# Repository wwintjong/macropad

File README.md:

# Macropad

My take on a macropad that I think will suit me. The layout is a 5x4 keys with hot-swappable switch and LED. Current iteration has no knobs or display implemented, but that is an idea for future versions. Next step is to design enclosure for the pad.

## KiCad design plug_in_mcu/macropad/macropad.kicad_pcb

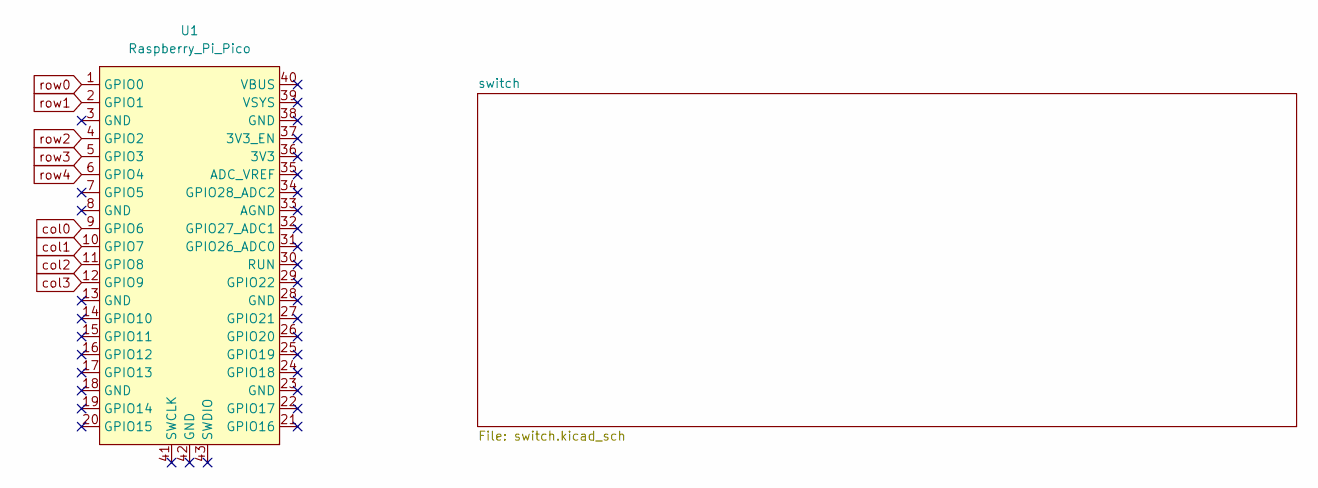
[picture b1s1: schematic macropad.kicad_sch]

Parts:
U1: Raspberry_Pi_Pico

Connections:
col0: U1.9 (GPIO6); also elsewhere on the board
col1: U1.10 (GPIO7); also elsewhere on the board
col2: U1.11 (GPIO8); also elsewhere on the board
col3: U1.12 (GPIO9); also elsewhere on the board
row0: U1.1 (GPIO0); also elsewhere on the board
row1: U1.2 (GPIO1); also elsewhere on the board
row2: U1.4 (GPIO2); also elsewhere on the board
row3: U1.5 (GPIO3); also elsewhere on the board
row4: U1.6 (GPIO4); also elsewhere on the board

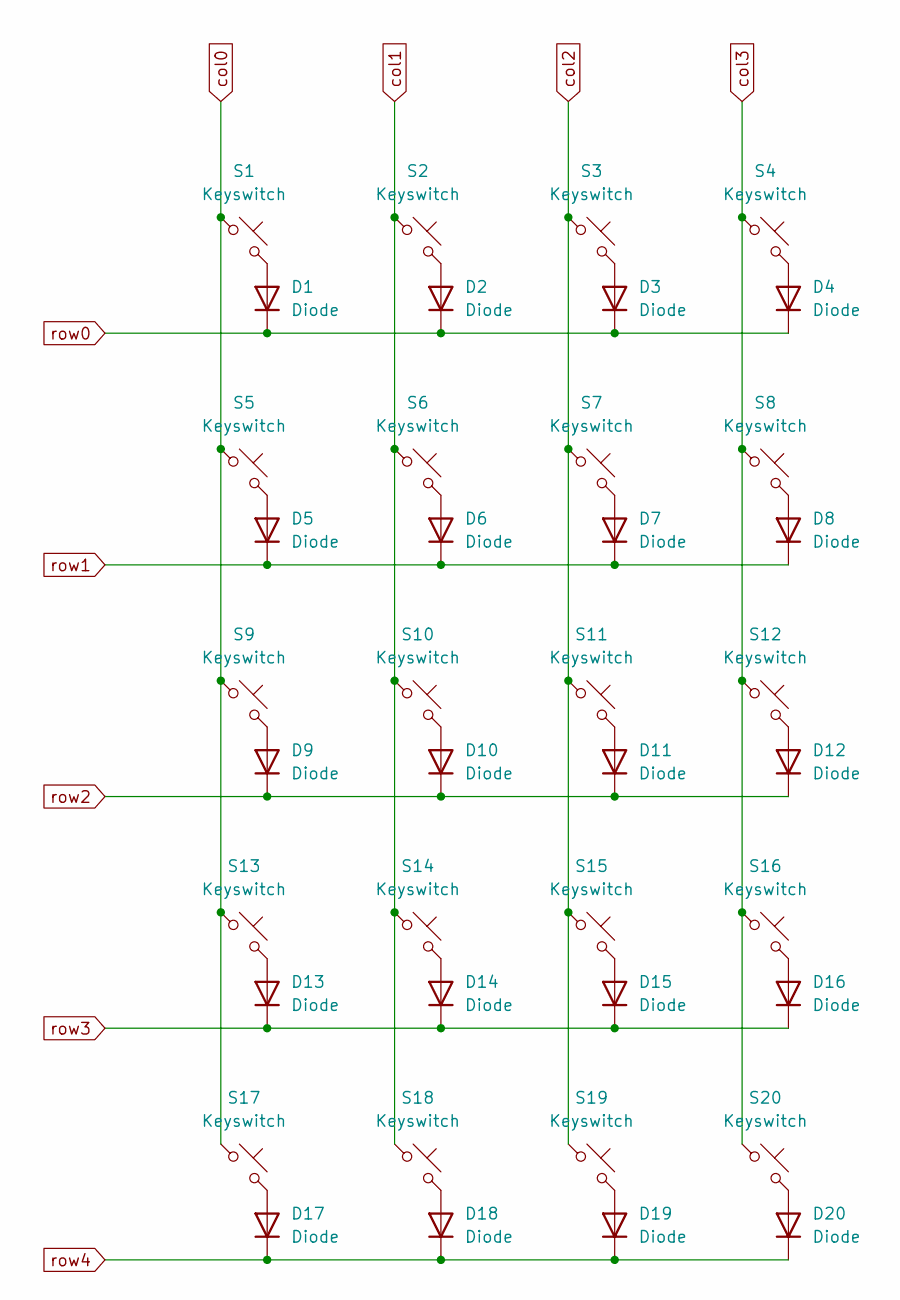
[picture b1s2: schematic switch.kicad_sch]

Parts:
D1, D2, D3, D4, D5, D6, D7, D8, D9, D10, D11, D12, D13, D14, D15, D16, D17, D18, D19, D20: Diode; D_SOD-123
S1, S2, S3, S4, S5, S6, S7, S8, S9, S10, S11, S12, S13, S14, S15, S16, S17, S18, S19, S20: Keyswitch; CherryMX_1.00u_KailhSocket

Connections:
unnamed: D1.2 (A), S1.2
unnamed: D2.2 (A), S2.2
unnamed: D3.2 (A), S3.2
unnamed: D4.2 (A), S4.2
unnamed: D5.2 (A), S5.2
unnamed: D6.2 (A), S6.2
unnamed: D7.2 (A), S7.2
unnamed: D8.2 (A), S8.2
unnamed: D9.2 (A), S9.2
unnamed: D10.2 (A), S10.2
unnamed: D11.2 (A), S11.2
unnamed: D12.2 (A), S12.2
unnamed: D13.2 (A), S13.2
unnamed: D14.2 (A), S14.2
unnamed: D15.2 (A), S15.2
unnamed: D16.2 (A), S16.2
unnamed: D17.2 (A), S17.2
unnamed: D18.2 (A), S18.2
unnamed: D19.2 (A), S19.2
unnamed: D20.2 (A), S20.2
col0: S1.1, S5.1, S9.1, S13.1, S17.1; also elsewhere on the board
col1: S2.1, S6.1, S10.1, S14.1, S18.1; also elsewhere on the board
col2: S3.1, S7.1, S11.1, S15.1, S19.1; also elsewhere on the board
col3: S4.1, S8.1, S12.1, S16.1, S20.1; also elsewhere on the board
row0: D1.1 (K), D2.1 (K), D3.1 (K), D4.1 (K); also elsewhere on the board
row1: D5.1 (K), D6.1 (K), D7.1 (K), D8.1 (K); also elsewhere on the board
row2: D9.1 (K), D10.1 (K), D11.1 (K), D12.1 (K); also elsewhere on the board
row3: D13.1 (K), D14.1 (K), D15.1 (K), D16.1 (K); also elsewhere on the board
row4: D17.1 (K), D18.1 (K), D19.1 (K), D20.1 (K); also elsewhere on the board

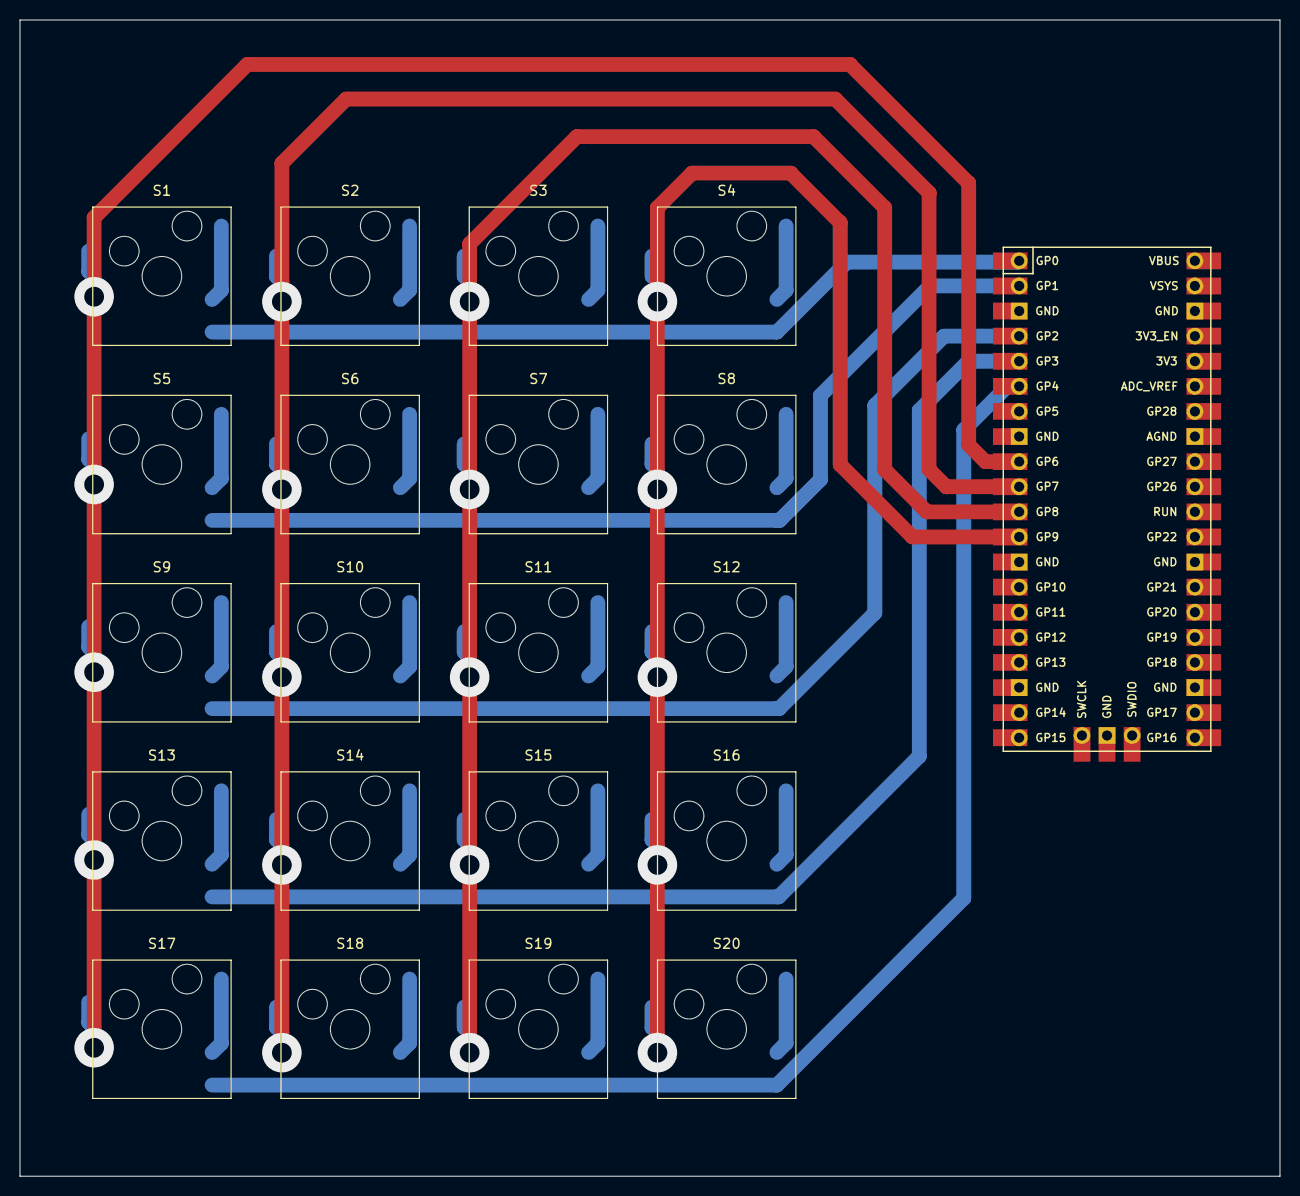
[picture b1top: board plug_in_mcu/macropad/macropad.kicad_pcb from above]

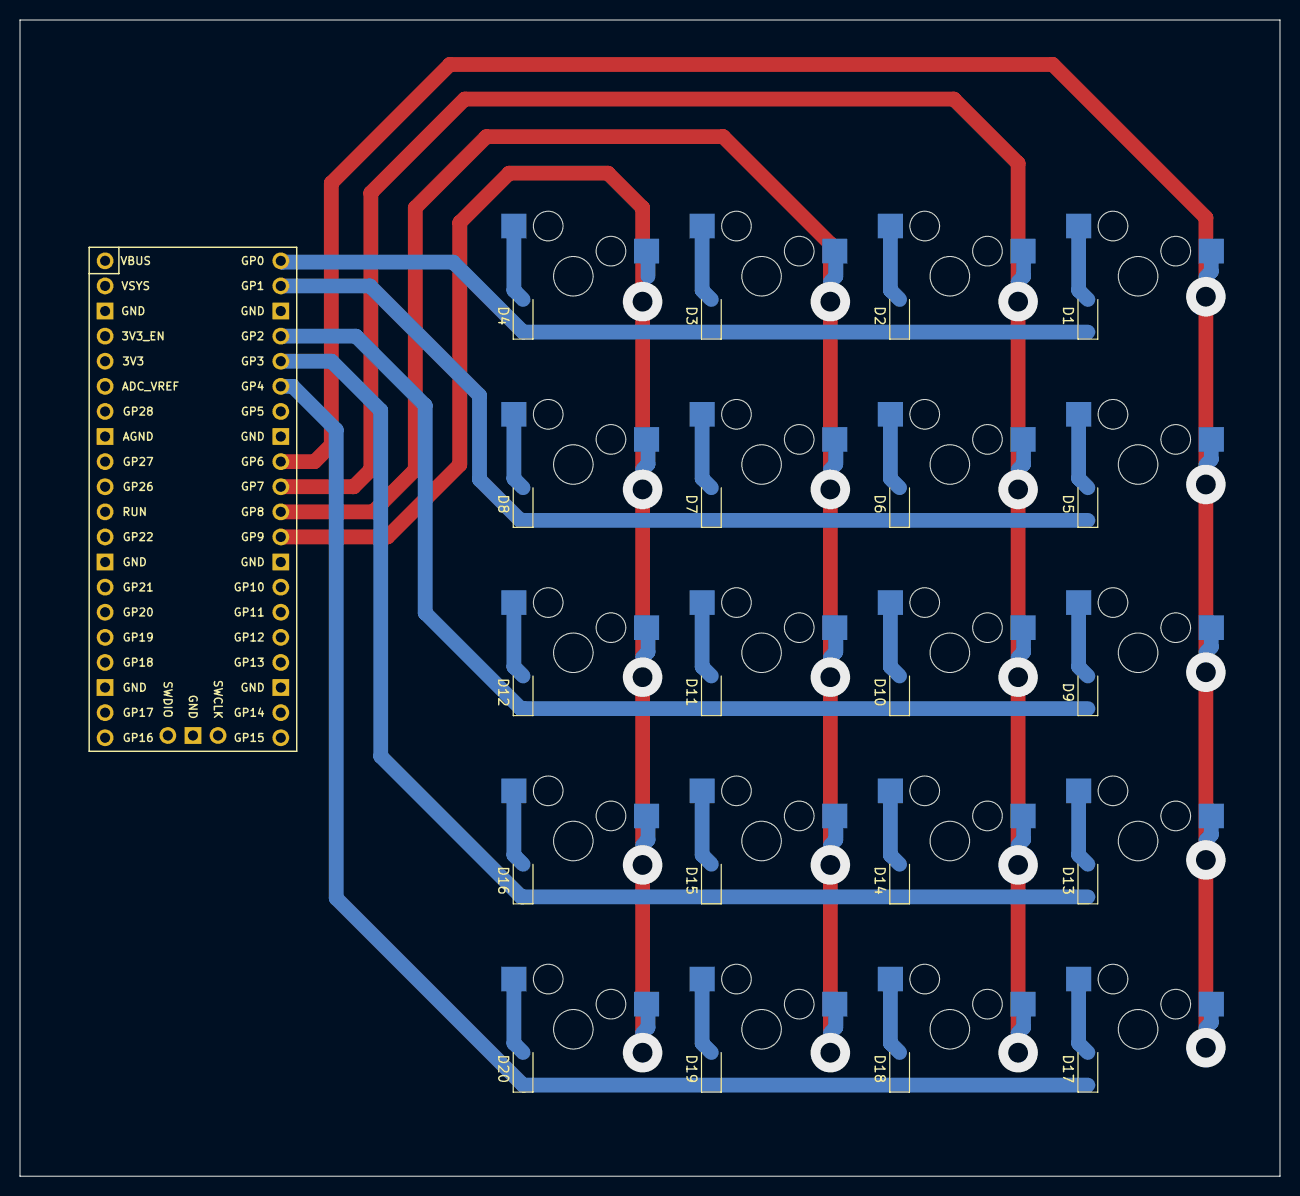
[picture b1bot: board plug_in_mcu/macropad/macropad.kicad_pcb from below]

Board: 2 copper layers, 127.5 x 117.0 mm, 41 parts (20 on the bottom side), 29 nets.

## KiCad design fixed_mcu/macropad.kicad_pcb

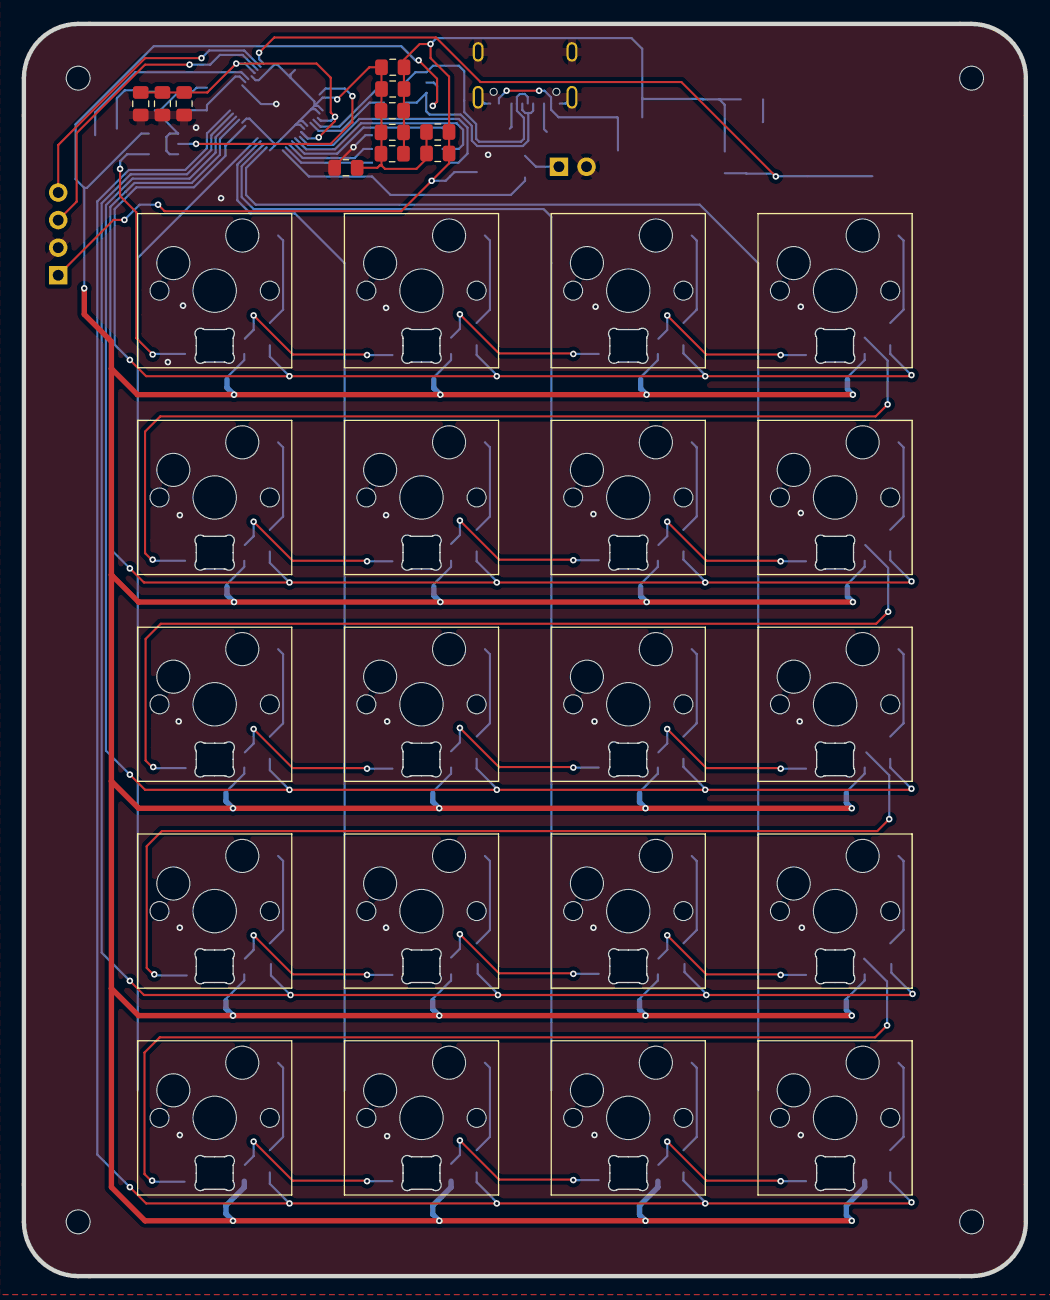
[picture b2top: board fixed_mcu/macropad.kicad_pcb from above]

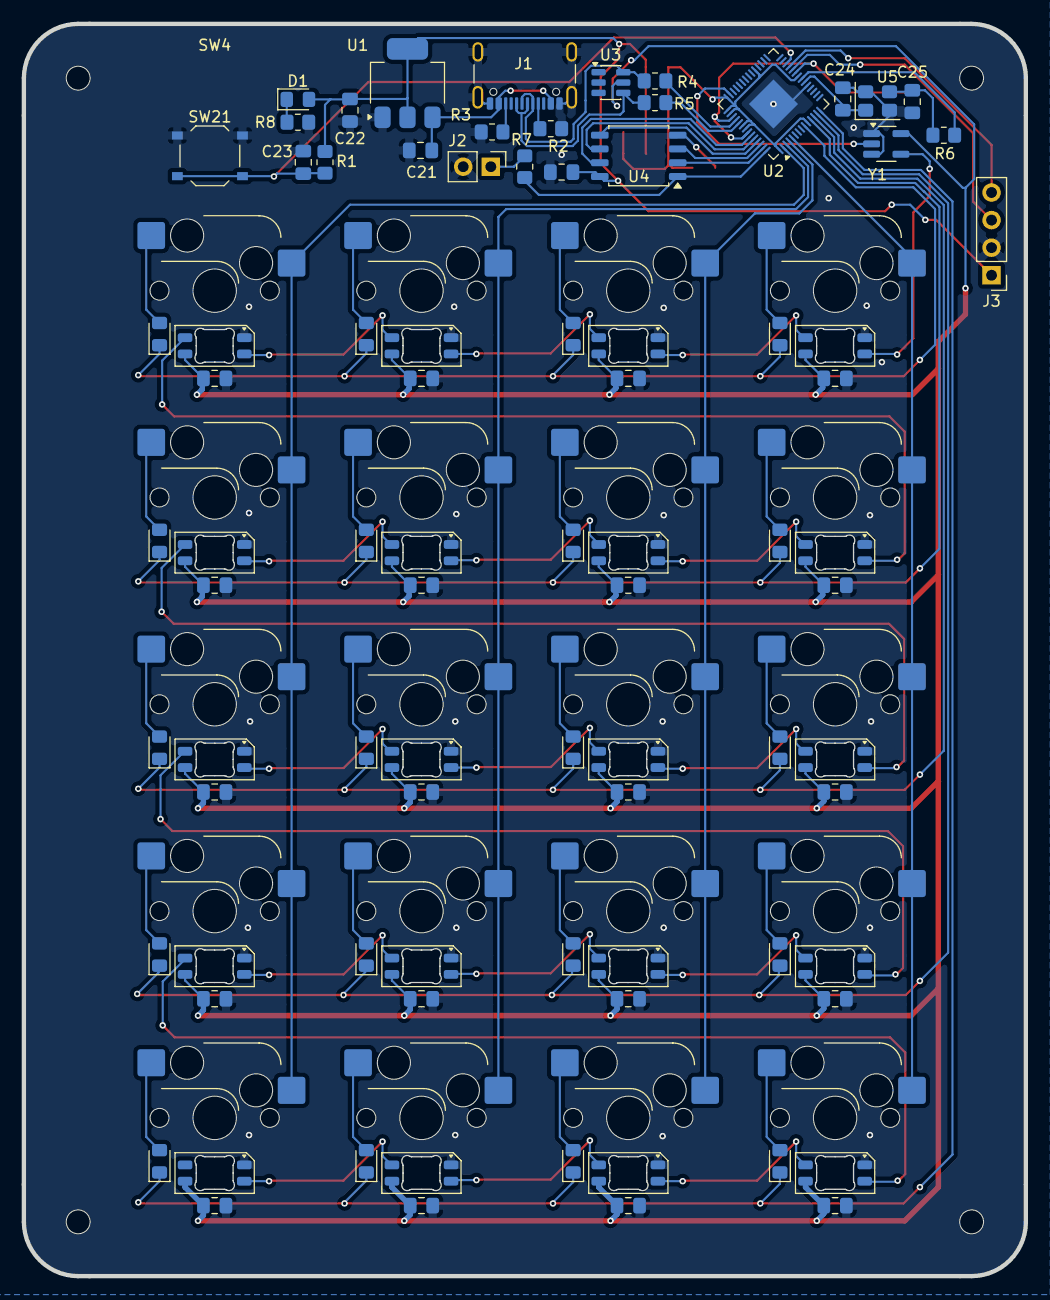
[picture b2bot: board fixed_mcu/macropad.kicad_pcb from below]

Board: 2 copper layers, 92.3 x 115.3 mm, 120 parts (85 on the bottom side), 76 nets.

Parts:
C1, C2, C3, C4, C5, C6, C7, C8, C9, C10, C11, C12, C13, C14, C15, C16, C17, C18, C19, C20, C23, C26, C27, C28, C29, C30, C31, C32, C33, C34, C35: 100nF; C_0805_2012Metric_Pad1.18x1.45mm_HandSolder
C21, C22: 10u; C_0805_2012Metric_Pad1.18x1.45mm_HandSolder
C24, C25: 30pF; C_0805_2012Metric_Pad1.18x1.45mm_HandSolder
C36, C37: 1uF; C_0805_2012Metric_Pad1.18x1.45mm_HandSolder
D1: LED; LED_0805_2012Metric_Pad1.15x1.40mm_HandSolder
D2, D3, D4, D5, D6, D7, D8, D9, D10, D11, D12, D13, D14, D15, D16, D17, D18, D19, D20, D21: D; D_0805_2012Metric_Pad1.15x1.40mm_HandSolder
H1, H2, H3, H4: MountingHole; MountingHole_2.2mm_M2
J1: USB_C_Receptacle_USB2.0_16P; USB_C_Receptacle_GCT_USB4105-xx-A_16P_TopMnt_Horizontal
J2: Conn_01x02; PinHeader_1x02_P2.54mm_Vertical
J3: Conn_01x04_Socket; PinHeader_1x04_P2.54mm_Vertical
L1, L2, L3, L4, L5, L6, L7, L8, L9, L10, L11, L12, L13, L14, L15, L16, L17, L18, L19, L20: SK6812MINI-E; LED_SK6812MINI-E_3.2x2.8mm_P1.5mm_ReverseMount
R1: 10k; R_0805_2012Metric_Pad1.20x1.40mm_HandSolder
R2, R3: 5.1k; R_0805_2012Metric_Pad1.20x1.40mm_HandSolder
R4, R5: 27; R_0805_2012Metric_Pad1.20x1.40mm_HandSolder
R6, R7: 1k; R_0805_2012Metric_Pad1.20x1.40mm_HandSolder
R8: 470; R_0805_2012Metric_Pad1.20x1.40mm_HandSolder
SW1, SW2, SW3, SW4, SW5, SW6, SW7, SW8, SW9, SW10, SW11, SW12, SW13, SW14, SW15, SW16, SW17, SW18, SW19, SW20: CherryMX; Hotswap_MX_1.00u
SW21: SW_Push; SW_Push_1P1T_XKB_TS-1187A
U1: NCP1117-3.3_SOT223; SOT-223-3_TabPin2
U2: RP2040; QFN-56-1EP_7x7mm_P0.4mm_EP3.2x3.2mm
U3: SRV05-4; SOT-23-6
U4: W25Q128JVS; SOIC-8_5.3x5.3mm_P1.27mm
U5: 74AHCT1G125; SOT-23-5_HandSoldering
Y1: Crystal_GND24; Crystal_SMD_Abracon_ABM8G-4Pin_3.2x2.5mm

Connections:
+1V1: C27.1, C28.1, C36.1, U2.23 (DVDD), U2.45 (VREG_VOUT), U2.50 (DVDD)
+3.3V: C22.1, C26.1, C29.1, C30.1, C31.1, C32.1, C33.1, C34.1, C35.1, D1.2 (A), J3.1, R1.1, U1.2 (VO), U4.8 (VCC)
+5V: C1.1, C2.1, C3.1, C4.1, C5.1, C6.1, C7.1, C8.1, C9.1, C10.1, C11.1, C12.1, C13.1, C14.1, C15.1, C16.1, C17.1, C18.1, C19.1, C20.1, L1.3 (VDD), L2.3 (VDD), L3.3 (VDD), L4.3 (VDD), L5.3 (VDD), L6.3 (VDD), L7.3 (VDD), L8.3 (VDD), L9.3 (VDD), L10.3 (VDD), L11.3 (VDD), L12.3 (VDD), L13.3 (VDD), L14.3 (VDD), L15.3 (VDD), L16.3 (VDD), L17.3 (VDD), L18.3 (VDD), L19.3 (VDD), L20.3 (VDD), U3.5 (VP), U5.5 (VCC)
/MCU/QSPI_SCLK: U2.52 (QSPI_SCLK), U4.6 (CLK)
/MCU/QSPI_SD0: U2.53 (QSPI_SD0), U4.5 (DI/IO_{0})
/MCU/QSPI_SD1: U2.55 (QSPI_SD1), U4.2 (DO/IO_{1})
/MCU/QSPI_SD2: U2.54 (QSPI_SD2), U4.3 (~WP/IO_{2})
/MCU/QSPI_SD3: U2.51 (QSPI_SD3), U4.7 (~HOLD/~RESET/IO_{3})
/MCU/QSPI_SS: R7.2, U2.56 (~QSPI_SS), U4.1 (~CS)
/MCU/RUN: C23.1, R1.2, SW21.1, U2.26 (RUN)
/MCU/SWCLK: J3.3, U2.24 (SWCLK)
/MCU/SWDIO: J3.4, U2.25 (SWDIO)
/MCU/USB_D+: J1.A6 (D+), J1.B6 (D+), R5.1, U3.4 (IO3)
/MCU/USB_D-: J1.A7 (D-), J1.B7 (D-), R4.1, U3.6 (IO4)
/MCU/VREG_IN: C29.2, C30.2, C31.2, C32.2, C33.2, C34.2, C35.2, C37.1, U2.1 (IOVDD), U2.10 (IOVDD), U2.22 (IOVDD), U2.33 (IOVDD), U2.42 (IOVDD), U2.43 (ADC_AVDD), U2.44 (VREG_VIN), U2.48 (USB_VDD), U2.49 (IOVDD)
/MCU/X_IN: C24.2, U2.20 (XIN), Y1.1
/MCU/X_OUT: R6.2, U2.21 (XOUT)
GND: C1.2, C2.2, C3.2, C4.2, C5.2, C6.2, C7.2, C8.2, C9.2, C10.2, C11.2, C12.2, C13.2, C14.2, C15.2, C16.2, C17.2, C18.2, C19.2, C20.2, C21.2, C22.2, C23.2, C24.1, C25.1, C26.2, C27.2, C28.2, C36.2, C37.2, J1.A1 (GND), J1.A12 (GND), J1.B1 (GND), J1.B12 (GND), J1.SH (SHIELD), J2.2, J3.2, L1.1 (VSS), L2.1 (VSS), L3.1 (VSS), L4.1 (VSS), L5.1 (VSS), L6.1 (VSS), L7.1 (VSS), L8.1 (VSS), L9.1 (VSS), L10.1 (VSS), L11.1 (VSS), L12.1 (VSS), L13.1 (VSS), L14.1 (VSS), L15.1 (VSS), L16.1 (VSS), L17.1 (VSS), L18.1 (VSS), L19.1 (VSS), L20.1 (VSS), R2.2, R3.2, R8.2, SW21.2, U1.1 (GND), U2.19 (TESTEN), U2.57 (GND), U3.2 (VN), U4.4 (GND), U5.1, U5.3 (GND), Y1.2 (G), Y1.4 (G)
In_3V3: U2.41 (GPIO29/ADC3), U5.2
unnamed: C25.2, R6.1, Y1.3
unnamed: D1.1 (K), R8.1
unnamed: D2.2 (A), SW1.2
unnamed: D3.2 (A), SW2.2
unnamed: D4.2 (A), SW3.2
unnamed: D5.2 (A), SW4.2
unnamed: D6.2 (A), SW5.2
unnamed: D7.2 (A), SW6.2
unnamed: D8.2 (A), SW7.2
unnamed: D9.2 (A), SW8.2
unnamed: D10.2 (A), SW9.2
unnamed: D11.2 (A), SW10.2
unnamed: D12.2 (A), SW11.2
unnamed: D13.2 (A), SW12.2
unnamed: D14.2 (A), SW13.2
unnamed: D15.2 (A), SW14.2
unnamed: D16.2 (A), SW15.2
unnamed: D17.2 (A), SW16.2
unnamed: D18.2 (A), SW17.2
unnamed: D19.2 (A), SW18.2
unnamed: D20.2 (A), SW19.2
unnamed: D21.2 (A), SW20.2
unnamed: J1.A5 (CC1), R2.1
unnamed: J1.B5 (CC2), R3.1
unnamed: J2.1, R7.1
unnamed: L1.4 (DOUT), L2.2 (DIN)
unnamed: L2.4 (DOUT), L3.2 (DIN)
unnamed: L3.4 (DOUT), L4.2 (DIN)
unnamed: L4.4 (DOUT), L5.2 (DIN)
unnamed: L5.4 (DOUT), L6.2 (DIN)
unnamed: L6.4 (DOUT), L7.2 (DIN)
unnamed: L7.4 (DOUT), L8.2 (DIN)
unnamed: L8.4 (DOUT), L9.2 (DIN)
unnamed: L9.4 (DOUT), L10.2 (DIN)
unnamed: L10.4 (DOUT), L11.2 (DIN)
unnamed: L11.4 (DOUT), L12.2 (DIN)
unnamed: L12.4 (DOUT), L13.2 (DIN)
unnamed: L13.4 (DOUT), L14.2 (DIN)
unnamed: L14.4 (DOUT), L15.2 (DIN)
unnamed: L15.4 (DOUT), L16.2 (DIN)
unnamed: L16.4 (DOUT), L17.2 (DIN)
unnamed: L17.4 (DOUT), L18.2 (DIN)
unnamed: L18.4 (DOUT), L19.2 (DIN)
unnamed: L19.4 (DOUT), L20.2 (DIN)
unnamed: R4.2, U2.46 (USB_DM)
unnamed: R5.2, U2.47 (USB_DP)
Out_5V: L1.2 (DIN), U5.4
VBUS: C21.1, J1.A4 (VBUS), J1.A9 (VBUS), J1.B4 (VBUS), J1.B9 (VBUS), U1.3 (VI)
col0: SW1.1, SW5.1, SW9.1, SW13.1, SW17.1, U2.5 (GPIO3)
col1: SW2.1, SW6.1, SW10.1, SW14.1, SW18.1, U2.4 (GPIO2)
col2: SW3.1, SW7.1, SW11.1, SW15.1, SW19.1, U2.3 (GPIO1)
col3: SW4.1, SW8.1, SW12.1, SW16.1, SW20.1, U2.2 (GPIO0)
row0: D2.1 (K), D3.1 (K), D4.1 (K), D5.1 (K), U2.9 (GPIO7)
row1: D6.1 (K), D7.1 (K), D8.1 (K), D9.1 (K), U2.11 (GPIO8)
row2: D10.1 (K), D11.1 (K), D12.1 (K), D13.1 (K), U2.12 (GPIO9)
row3: D14.1 (K), D15.1 (K), D16.1 (K), D17.1 (K), U2.13 (GPIO10)
row4: D18.1 (K), D19.1 (K), D20.1 (K), D21.1 (K), U2.14 (GPIO11)
